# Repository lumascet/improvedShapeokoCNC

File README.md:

# Improved Shapeoko CNC Mill

:warning: the schematics file is incomplete and has errors which are listed in PATCHNOTES.txt :warning:

This repository contains the config file for g2core as well as the shield schematics for arduino due.

See https://github.com/synthetos/g2 for the g2core project.

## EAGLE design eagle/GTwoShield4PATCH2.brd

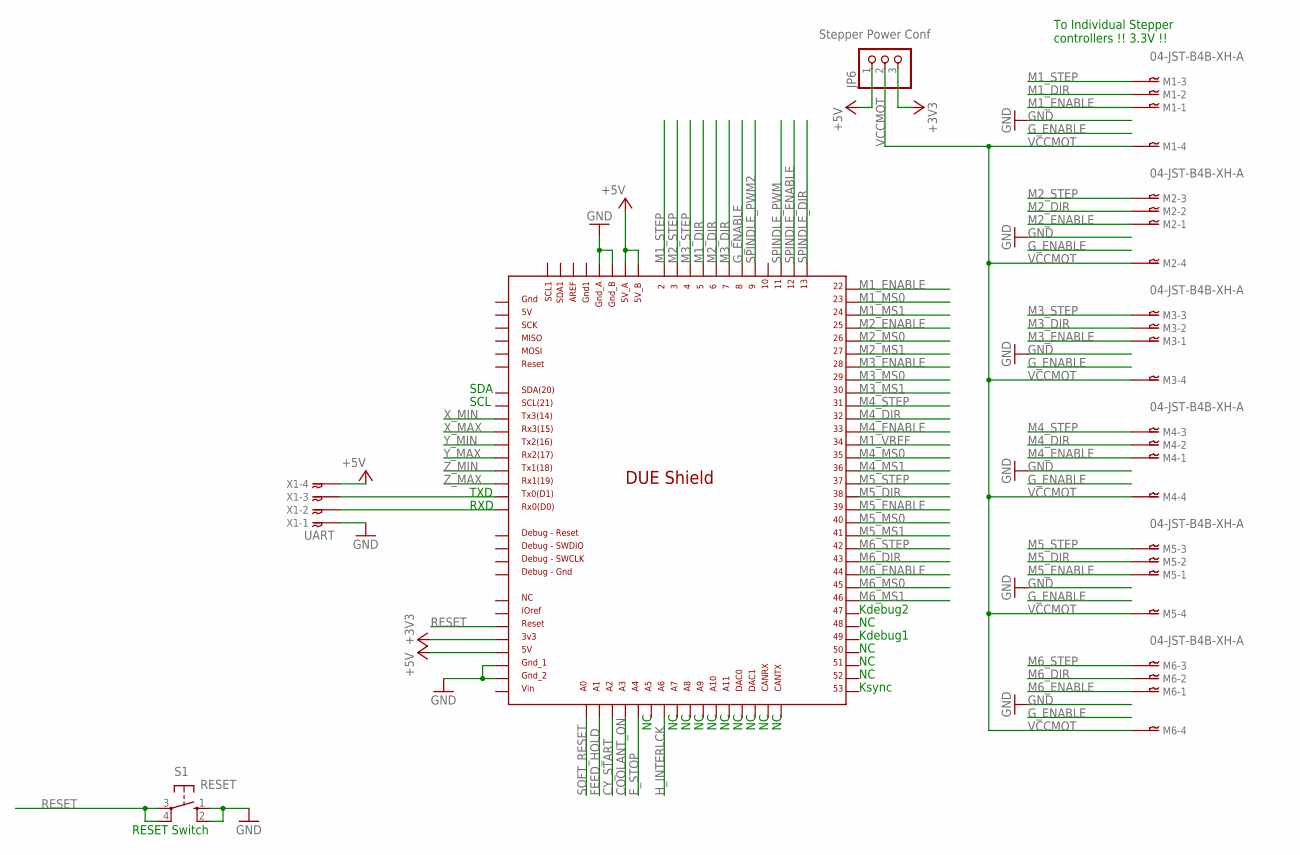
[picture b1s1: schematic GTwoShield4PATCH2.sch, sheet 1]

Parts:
JP6: Stepper Power Conf; 1X03
M1, M2, M3, M4, M5, M6: 04-JST-B4B-XH-A; B4B-XH
S1: RESET; B3F-10XX
U$1: DUE(NORMAL)
X1: UART; B4B-XH

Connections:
+3V3: JP6.3, U$1.3V3; also elsewhere on the board
+5V: JP6.1, U$1.5V, U$1.5V_A, U$1.5V_B, X1.P$4; also elsewhere on the board
COOLANT_ON: U$1.A3; also elsewhere on the board
CY_START: U$1.A2; also elsewhere on the board
E_STOP: U$1.A4; also elsewhere on the board
FEED_HOLD: U$1.A1; also elsewhere on the board
GND: S1.1 (S), S1.2 (S1), U$1.GND_1, U$1.GND_2, U$1.GND_A, U$1.GND_B, X1.P$1; also elsewhere on the board
G_ENABLE: U$1.8
H_INTERLCK: U$1.A6
M1_DIR: M1.P$2, U$1.5
M1_ENABLE: M1.P$1, U$1.22
M1_MS0: U$1.23
M1_MS1: U$1.24
M1_STEP: M1.P$3, U$1.2
M1_VREF: U$1.34
M2_DIR: M2.P$2, U$1.6
M2_ENABLE: M2.P$1, U$1.25
M2_MS0: U$1.26
M2_MS1: U$1.27
M2_STEP: M2.P$3, U$1.3
M3_DIR: M3.P$2, U$1.7
M3_ENABLE: M3.P$1, U$1.28
M3_MS0: U$1.29
M3_MS1: U$1.30
M3_STEP: M3.P$3, U$1.4
M4_DIR: M4.P$2, U$1.32
M4_ENABLE: M4.P$1, U$1.33
M4_MS0: U$1.35
M4_MS1: U$1.36
M4_STEP: M4.P$3, U$1.31
M5_DIR: M5.P$2, U$1.38
M5_ENABLE: M5.P$1, U$1.39
M5_MS0: U$1.40
M5_MS1: U$1.41
M5_STEP: M5.P$3, U$1.37
M6_DIR: M6.P$2, U$1.43
M6_ENABLE: M6.P$1, U$1.44
M6_MS0: U$1.45
M6_MS1: U$1.46
M6_STEP: M6.P$3, U$1.42
unnamed: U$1.TX0, X1.P$3
unnamed: U$1.RX0, X1.P$2
RESET: S1.3, S1.4 (P1), U$1.RESET
SOFT_RESET: U$1.A0; also elsewhere on the board
SPINDLE_DIR: U$1.13; also elsewhere on the board
SPINDLE_ENABLE: U$1.12; also elsewhere on the board
SPINDLE_PWM: U$1.11; also elsewhere on the board
SPINDLE_PWM2: U$1.9
VCCMOT: JP6.2, M1.P$4, M2.P$4, M3.P$4, M4.P$4, M5.P$4, M6.P$4
X_MAX: U$1.RX3; also elsewhere on the board
X_MIN: U$1.TX3; also elsewhere on the board
Y_MAX: U$1.RX2; also elsewhere on the board
Y_MIN: U$1.TX2; also elsewhere on the board
Z_MAX: U$1.RX1; also elsewhere on the board
Z_MIN: U$1.TX1; also elsewhere on the board

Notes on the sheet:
Kdebug2
Kdebug1
Ksync
SDA
SCL
TXD
RXD
To Individual Stepper controllers !! 3.3V !!
RESET Switch

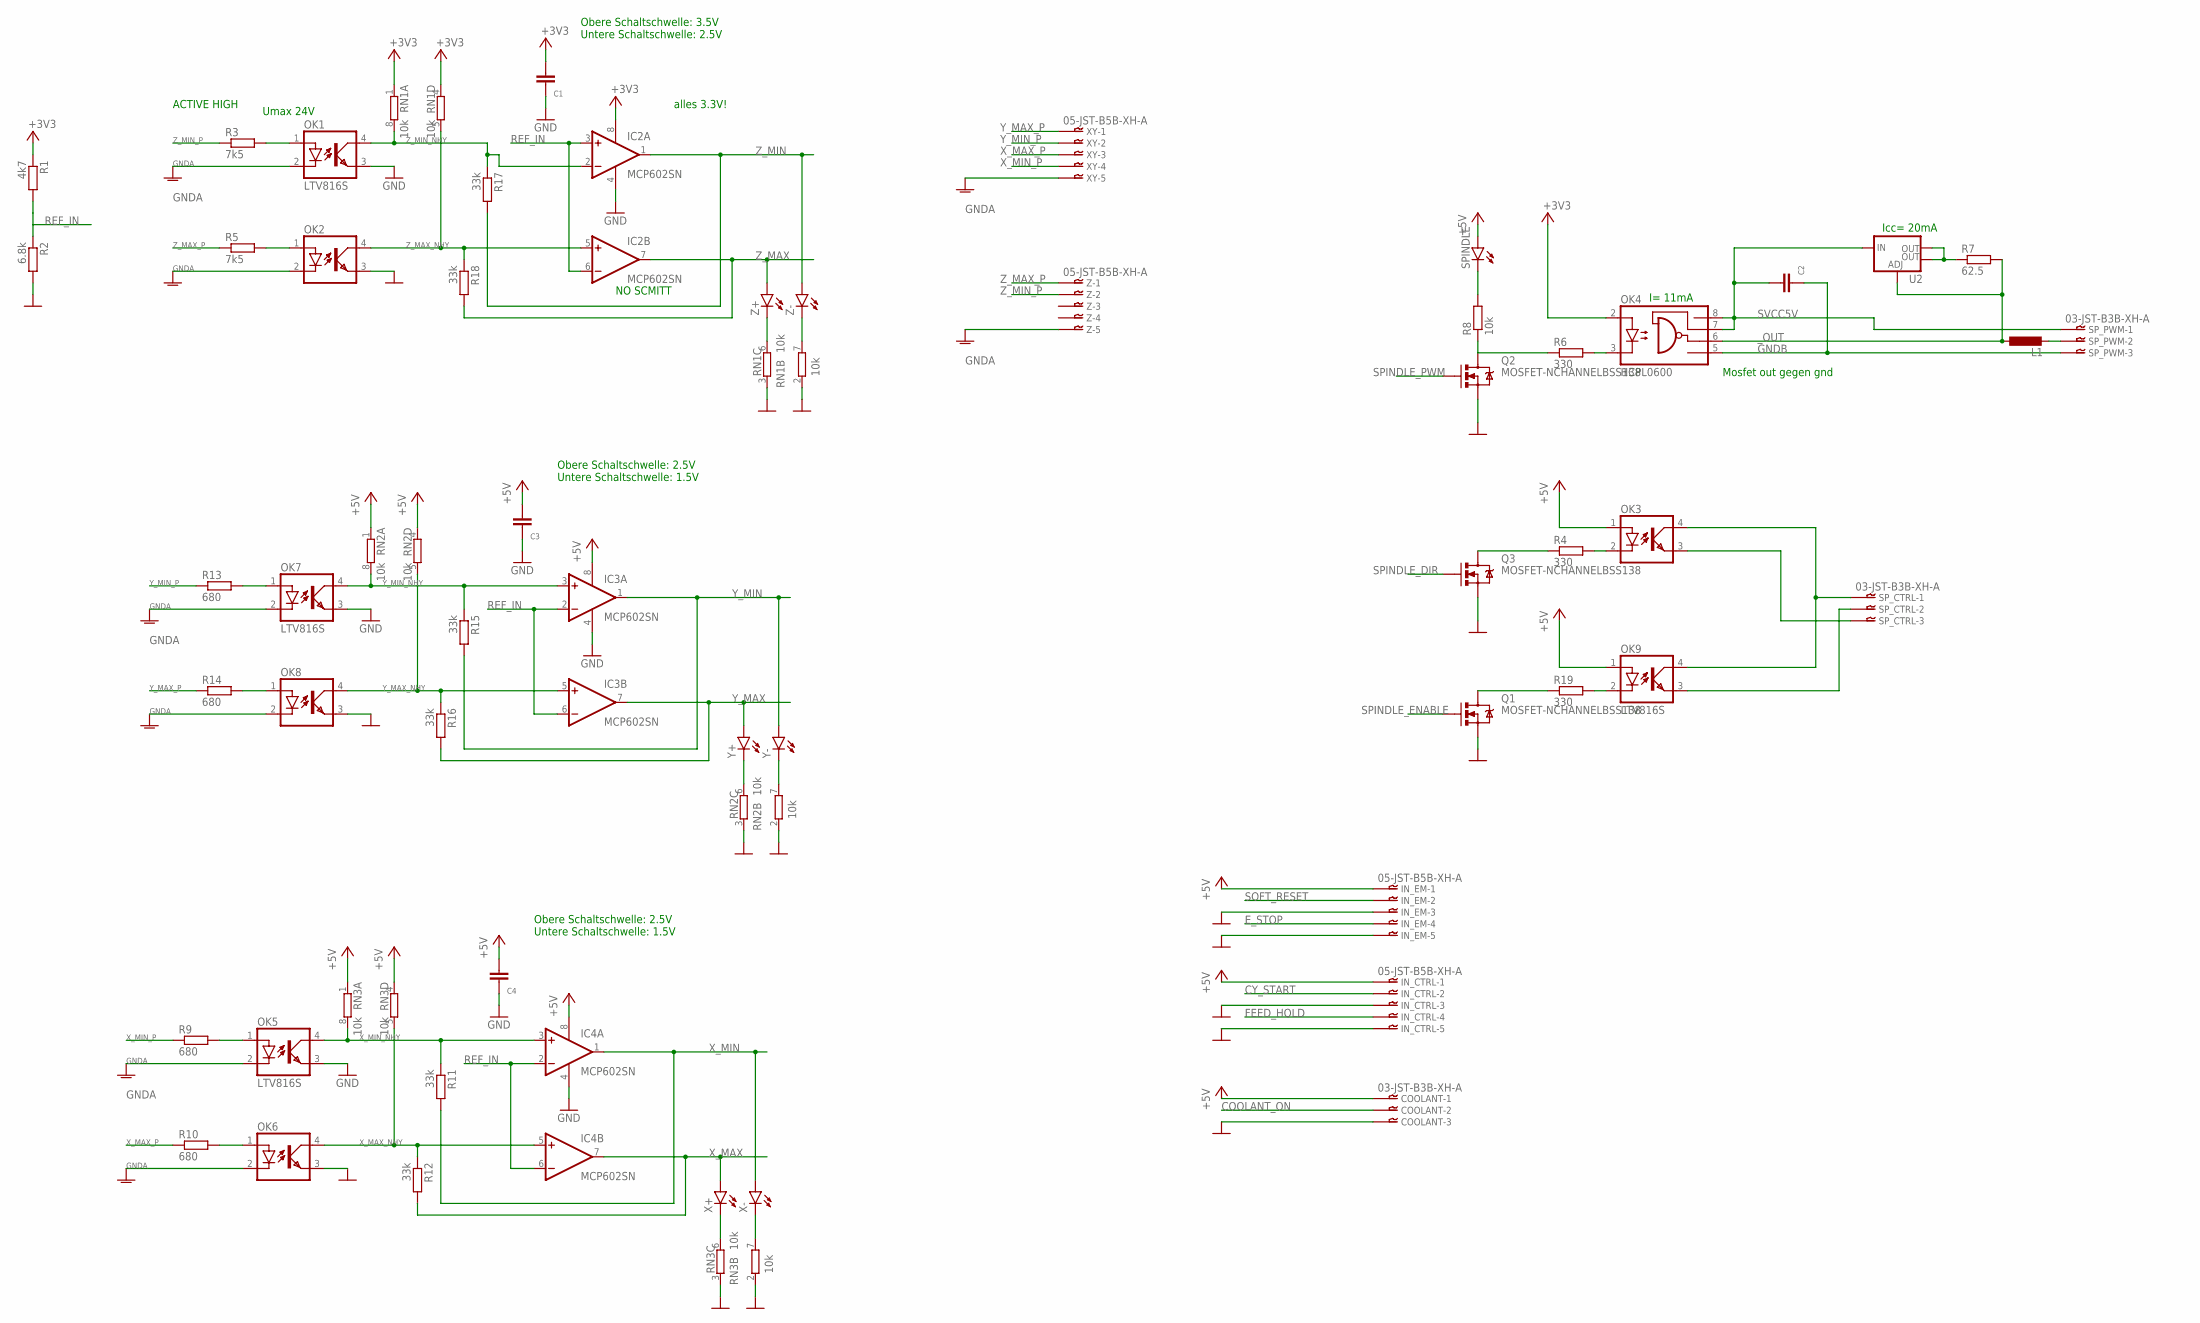
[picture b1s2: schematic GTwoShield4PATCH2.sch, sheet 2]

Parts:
C1, C2, C3, C4: 100nf; C0603K
COOLANT: 03-JST-B3B-XH-A; B3B-XH
IC2, IC3, IC4: MCP602SN; SO08
IN_CTRL: 05-JST-B5B-XH-A; B5B-XH
IN_EM: 05-JST-B5B-XH-A; B5B-XH
L1: L-EU0207/10; 0207/10
OK1, OK2, OK3, OK5, OK6, OK7, OK8, OK9: LTV816S; DIL4-SMD
OK4: HCPL0600; SOIC08
Q1, Q2, Q3: MOSFET-NCHANNELBSS138; SOT23
R1: 4k7; R0805
R2: 6.8k; R0805
R3, R5: 7k5; R0805
R4, R6, R19: 330; R0805
R7: 62.5; R0805
R8: 10k; R0805
R9, R10, R13, R14: 680; R0805
R11, R12, R15, R16, R17, R18: 33k; R0805
RN1, RN2, RN3: 10k; 0603-ARC
SPINDLE: LEDCHIP-LED0805; CHIP-LED0805
SP_CTRL: 03-JST-B3B-XH-A; B3B-XH
SP_PWM: 03-JST-B3B-XH-A; B3B-XH
U2: V_REG_LM1117SOT223; SOT223
X+: LEDCHIP-LED0805; CHIP-LED0805
X-: LEDCHIP-LED0805; CHIP-LED0805
XY: 05-JST-B5B-XH-A; B5B-XH
Y+: LEDCHIP-LED0805; CHIP-LED0805
Y-: LEDCHIP-LED0805; CHIP-LED0805
Z: 05-JST-B5B-XH-A; B5B-XH
Z+: LEDCHIP-LED0805; CHIP-LED0805
Z-: LEDCHIP-LED0805; CHIP-LED0805

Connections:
+3V3: C1.2, IC2.8 (V+), OK4.2 (A), R1.1, RN1.1, RN1.4 (1); also elsewhere on the board
+5V: C3.2, C4.2, COOLANT.P$1, IC3.8 (V+), IC4.8 (V+), IN_CTRL.P$1, IN_EM.P$1, OK3.1 (A), OK9.1 (A), RN2.1, RN2.4 (1), RN3.1, RN3.4 (1), SPINDLE.A; also elsewhere on the board
COOLANT_ON: COOLANT.P$2; also elsewhere on the board
CY_START: IN_CTRL.P$2; also elsewhere on the board
E_STOP: IN_EM.P$4; also elsewhere on the board
FEED_HOLD: IN_CTRL.P$4; also elsewhere on the board
GND: C1.1, C3.1, C4.1, COOLANT.P$3, IC2.4 (V-), IC3.4 (V-), IC4.4 (V-), IN_CTRL.P$3, IN_CTRL.P$5, IN_EM.P$3, IN_EM.P$5, OK1.3 (EMIT), OK2.3 (EMIT), OK5.3 (EMIT), OK6.3 (EMIT), OK7.3 (EMIT), OK8.3 (EMIT), Q1.2 (S), Q2.2 (S), Q3.2 (S), R2.2, RN1.2 (1), RN1.3 (1), RN2.2 (1), RN2.3 (1), RN3.2 (1), RN3.3 (1); also elsewhere on the board
GNDA: OK1.2 (C), OK2.2 (C), OK5.2 (C), OK6.2 (C), OK7.2 (C), OK8.2 (C), XY.P$5, Z.P$5
GNDB: C2.1, OK4.5 (GND), SP_PWM.P$3
unnamed: RN1.6 (2), Z+.C
unnamed: OK1.1 (A), R3.2
unnamed: OK2.1 (A), R5.2
unnamed: RN1.7 (2), Z-.C
unnamed: OK9.2 (C), R19.2
unnamed: Q1.3 (D), R19.1
unnamed: OK4.3 (C), R6.2
unnamed: OK5.1 (A), R9.2
unnamed: OK6.1 (A), R10.2
unnamed: OK7.1 (A), R13.2
unnamed: OK8.1 (A), R14.2
unnamed: RN2.6 (2), Y+.C
unnamed: RN2.7 (2), Y-.C
unnamed: RN3.6 (2), X+.C
unnamed: RN3.7 (2), X-.C
unnamed: Q2.3 (D), R6.1, R8.1
unnamed: OK3.3 (EMIT), SP_CTRL.P$3
unnamed: L1.2, SP_PWM.P$2
unnamed: R8.2, SPINDLE.C
unnamed: OK3.2 (C), R4.2
unnamed: Q3.3 (D), R4.1
unnamed: R7.1, U2.2 (OUT), U2.4 (OUT)
unnamed: OK3.4 (COL), OK9.4 (COL), SP_CTRL.P$1
unnamed: OK9.3 (EMIT), SP_CTRL.P$2
REF_IN: IC2.3 (+IN), IC2.6 (-IN), IC3.2 (-IN), IC3.6 (-IN), IC4.2 (-IN), IC4.6 (-IN), R1.2, R2.1
SOFT_RESET: IN_EM.P$2; also elsewhere on the board
SPINDLE_DIR: Q3.1 (G); also elsewhere on the board
SPINDLE_ENABLE: Q1.1 (G); also elsewhere on the board
SPINDLE_PWM: Q2.1 (G); also elsewhere on the board
SVCC5V: C2.2, OK4.7 (VE), OK4.8 (VCC), SP_PWM.P$1, U2.3 (IN)
X_MAX: IC4.7 (OUT), R12.2, X+.A; also elsewhere on the board
X_MAX_NHY: IC4.5 (+IN), OK6.4 (COL), R12.1, RN3.5 (2)
X_MAX_P: R10.1, XY.P$3
X_MIN: IC4.1 (OUT), R11.2, X-.A; also elsewhere on the board
X_MIN_NHY: IC4.3 (+IN), OK5.4 (COL), R11.1, RN3.8 (2)
X_MIN_P: R9.1, XY.P$4
Y_MAX: IC3.7 (OUT), R16.2, Y+.A; also elsewhere on the board
Y_MAX_NHY: IC3.5 (+IN), OK8.4 (COL), R16.1, RN2.5 (2)
Y_MAX_P: R14.1, XY.P$1
Y_MIN: IC3.1 (OUT), R15.2, Y-.A; also elsewhere on the board
Y_MIN_NHY: IC3.3 (+IN), OK7.4 (COL), R15.1, RN2.8 (2)
Y_MIN_P: R13.1, XY.P$2
Z_MAX: IC2.7 (OUT), R18.2, Z+.A; also elsewhere on the board
Z_MAX_NHY: IC2.5 (+IN), OK2.4 (COL), R18.1, RN1.5 (2)
Z_MAX_P: R5.1, Z.P$1
Z_MIN: IC2.1 (OUT), R17.2, Z-.A; also elsewhere on the board
Z_MIN_NHY: IC2.2 (-IN), OK1.4 (COL), R17.1, RN1.8 (2)
Z_MIN_P: R3.1, Z.P$2
_OUT: L1.1, OK4.6 (VO), R7.2, U2.1 (ADJ)

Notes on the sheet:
Obere Schaltschwelle: 3.5V Untere Schaltschwelle: 2.5V
Obere Schaltschwelle: 2.5V Untere Schaltschwelle: 1.5V
ACTIVE HIGH
I= 11mA
Umax 24V
Mosfet out gegen gnd
Icc= 20mA
alles 3.3V!
NO SCMITT

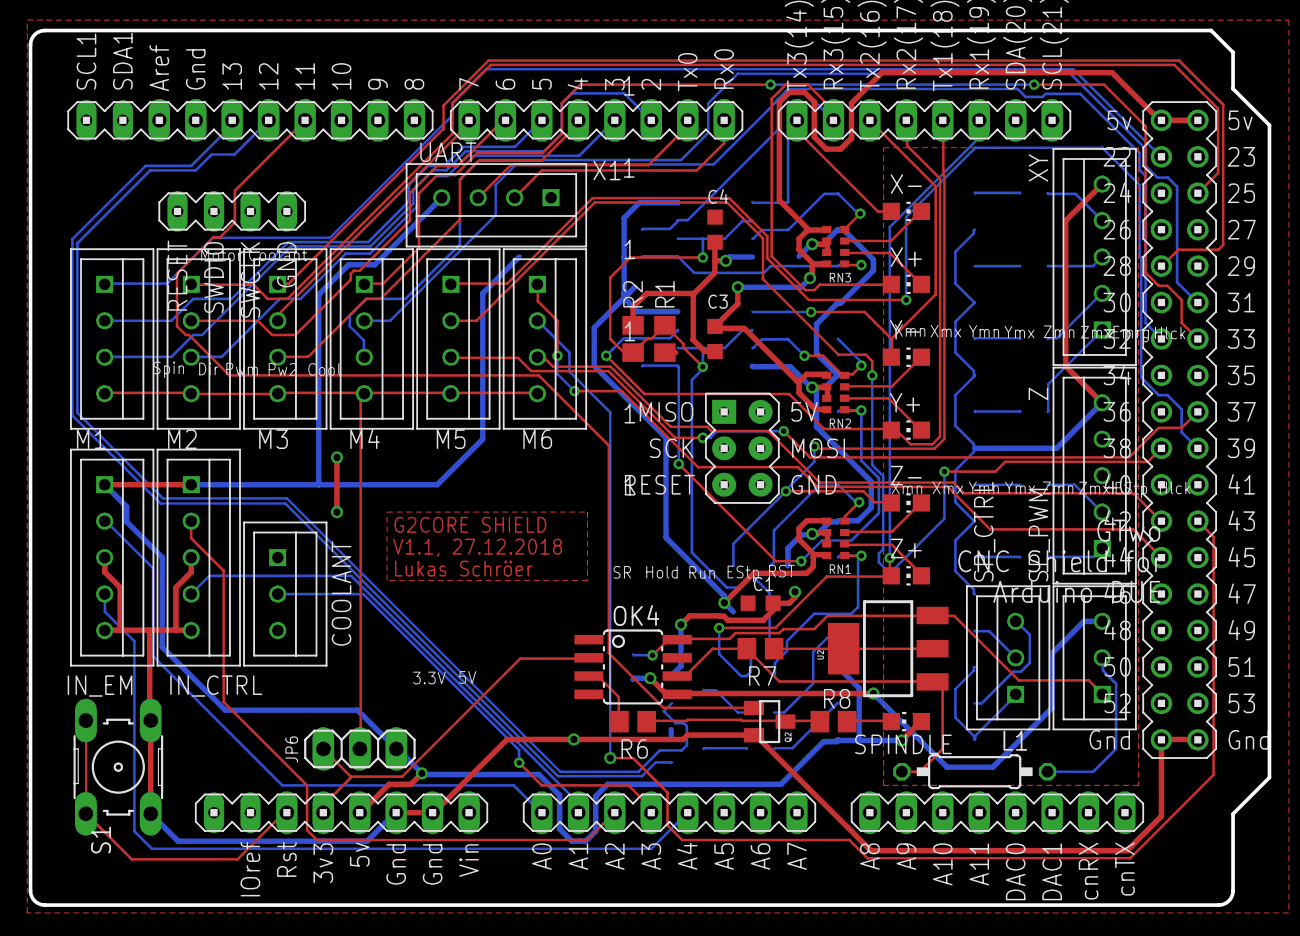
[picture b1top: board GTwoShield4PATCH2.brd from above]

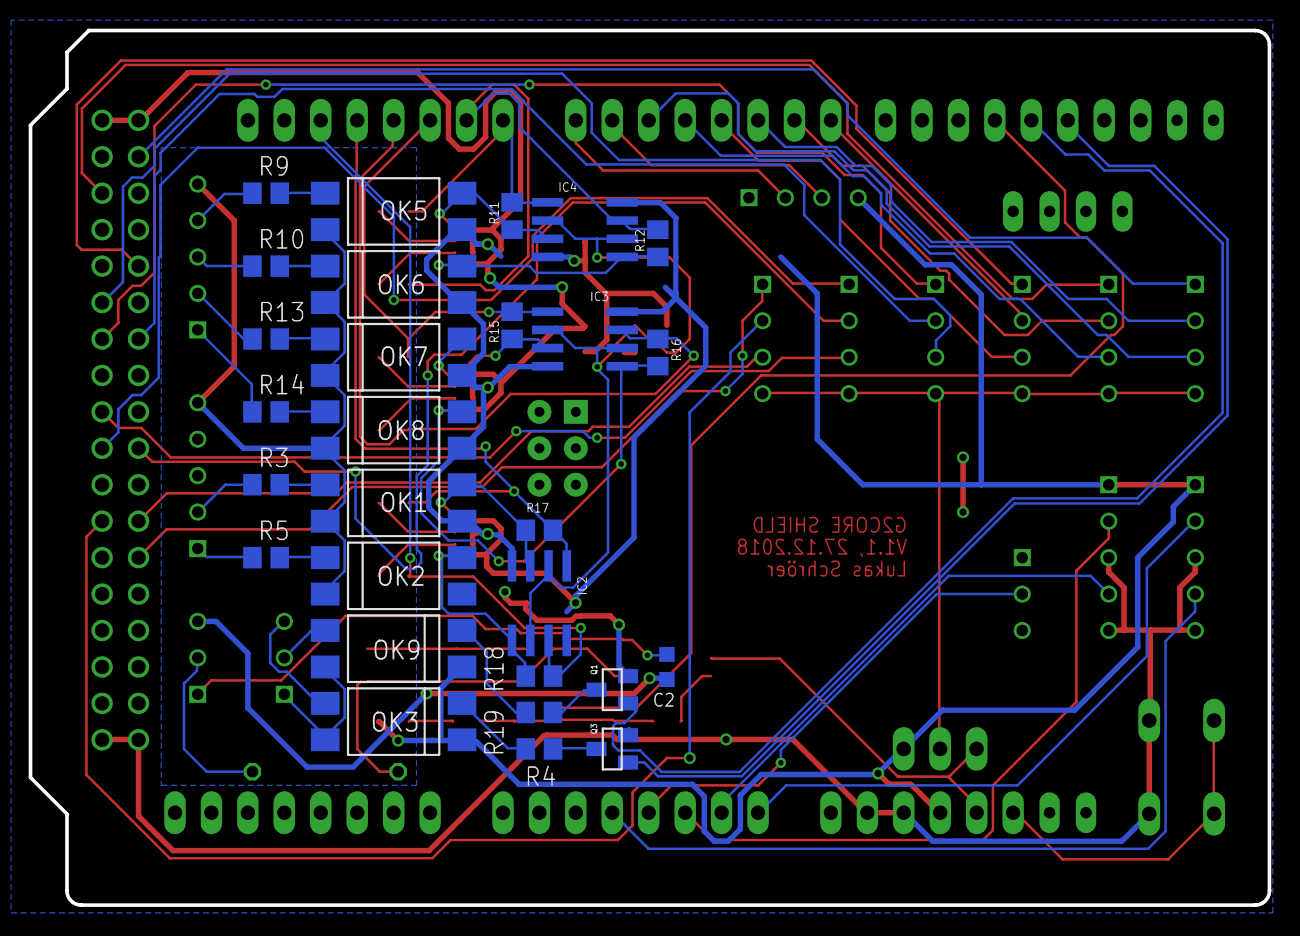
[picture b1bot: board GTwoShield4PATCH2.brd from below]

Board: 2 copper layers, 86.4 x 61.0 mm, 67 parts (28 on the bottom side), 80 nets.

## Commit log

2020-01-19 added disclaimer
2020-03-26 added g2core config
2020-03-26 fixed sh
2020-03-26 added depecndencies
2020-03-26 added sh scripts for automated build and upload
2020-03-26 updated files
2020-03-26 changed spindle pins
2020-09-11 updated to edge-preview with feedrate overrides
2020-09-11 bugfix
2020-09-11 optimized machine settings
2020-09-12 updated settings
2020-12-15 fixed config error for stable g2core-edge

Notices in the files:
parts and their libraries:
SparkFun-IC-Power: Licensing: Creative Commons ShareAlike 4.0 International - https://creativecommons.org/licenses/by-sa/4.0
